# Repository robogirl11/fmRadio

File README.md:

# My first FM radio!
Using Hackclub's Static as a guide for the pcb and schematic I worked on making an FM radio. Since this was my first time the guide was really helpful. I will be using the kit so I don't need to buy any parts. (thats why theres no BOM) I worked on this for around 4.5 hours. It is able to go to channels between 87.5-108.0. I will update this when I get it built with a photo. So far I have the photos of the pcb, schematic, & the 3d modeled pcb. I didn't make a case since I have an AM radio without a case and I like the look without the case so I didn't feel the need to make it. I think it also looks cooler that way.

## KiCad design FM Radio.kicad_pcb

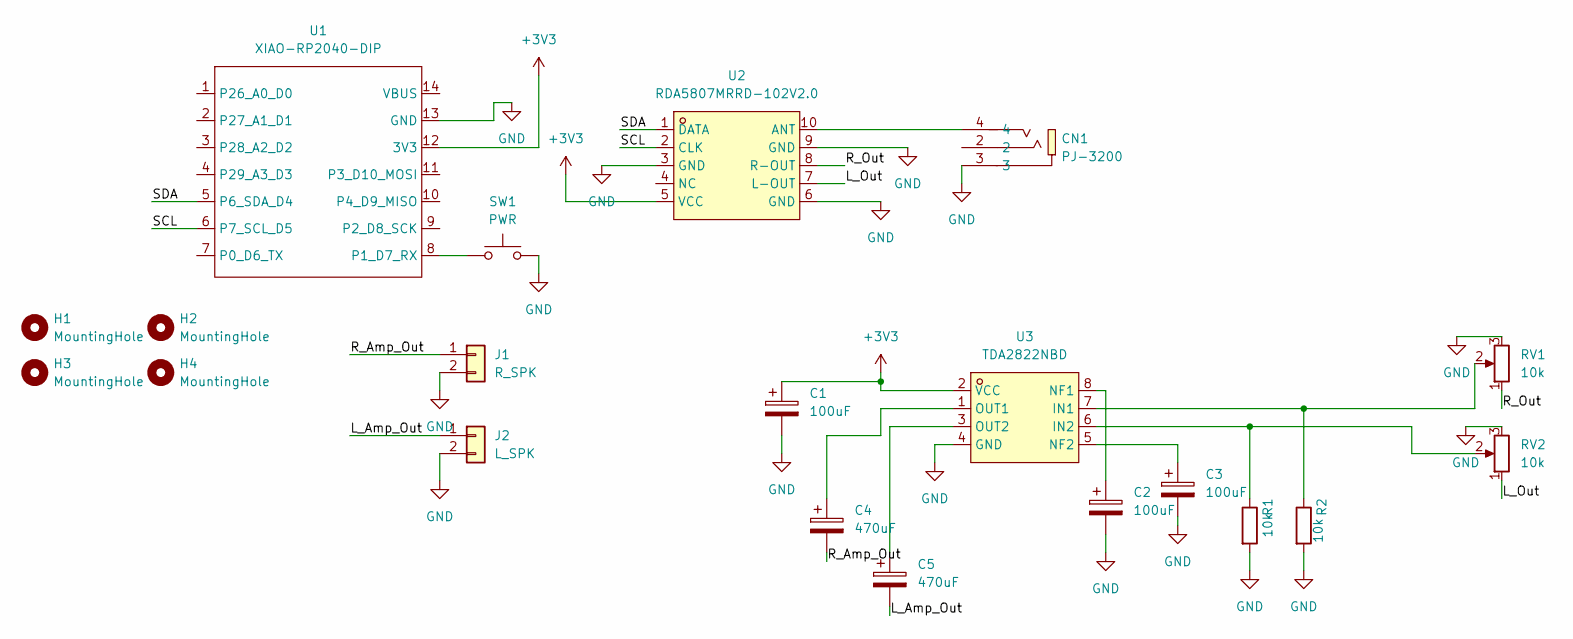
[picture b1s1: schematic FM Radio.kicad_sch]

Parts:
C1, C2, C3: 100uF; CP_Radial_D6.3mm_P2.50mm
C4, C5: 470uF; CP_Radial_D6.3mm_P2.50mm
CN1: PJ-3200; AUDIO-TH_PJ-3200; MPN PJ-3200; LCSC Part C2689690
H1, H2, H3, H4: MountingHole; MountingHole_2.7mm_M2.5
J1: R_SPK; PinHeader_1x02_P2.54mm_Vertical
J2: L_SPK; PinHeader_1x02_P2.54mm_Vertical
R1, R2: 10k; R_Axial_DIN0207_L6.3mm_D2.5mm_P7.62mm_Horizontal
RV1, RV2: 10k; PinHeader_1x03_P2.54mm_Vertical
SW1: PWR; PinHeader_1x02_P2.54mm_Vertical
U1: XIAO-RP2040-DIP
U2: RDA5807MRRD-102V2.0; RDA5807; MPN RDA5807MRRD-102V2.0; LCSC Part C9900205627
U3: TDA2822NBD; DIP-8_W7.62mm; MPN TDA2822NBD; LCSC Part C51927337

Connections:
+3V3: C1.1, U1.12 (3V3), U2.5 (VCC), U3.2 (VCC)
/L_Amp_Out: C5.2, J2.1
/L_Out: RV2.1, U2.7 (L-OUT)
/R_Amp_Out: C4.2, J1.1
/R_Out: RV1.1, U2.8 (R-OUT)
/SCL: U1.6 (P7_SCL_D5), U2.2 (CLK)
/SDA: U1.5 (P6_SDA_D4), U2.1 (DATA)
GND: C1.2, C2.2, C3.2, CN1.3, J1.2, J2.2, R1.2, R2.2, RV1.3, RV2.3, SW1.2, U1.13 (GND), U2.3 (GND), U2.6 (GND), U2.9 (GND), U3.4 (GND)
unnamed: SW1.1, U1.8 (P1_D7_RX)
unnamed: CN1.4, U2.10 (ANT)
unnamed: R2.1, RV1.2, U3.7 (IN1)
unnamed: R1.1, RV2.2, U3.6 (IN2)
unnamed: C2.1, U3.8 (NF1)
unnamed: C3.1, U3.5 (NF2)
unnamed: C4.1, U3.1 (OUT1)
unnamed: C5.1, U3.3 (OUT2)

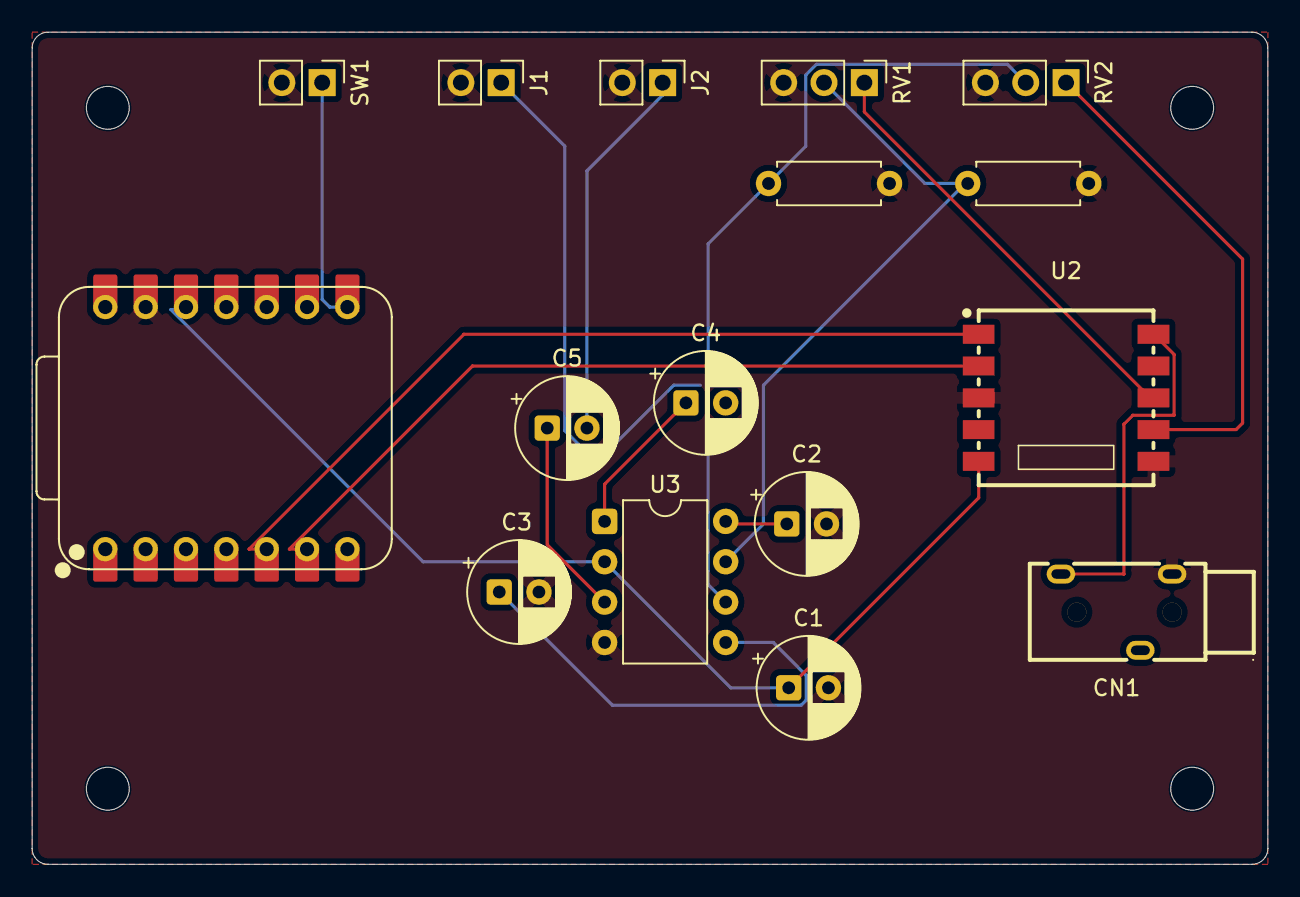
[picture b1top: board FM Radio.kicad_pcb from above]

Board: 2 copper layers, 77.8 x 52.4 mm, 20 parts (0 on the bottom side), 16 nets.
